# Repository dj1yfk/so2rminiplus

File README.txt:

SO2R MiniPlus - A simple and low cost SO2R controller

by Fabian Kurz, DJ5CW <fabian@fkurz.net>

Homepage:   https://fkurz.net/ham/so2rminiplus/
Repository: https://git.fkurz.net/dj1yfk/so2rminiplus

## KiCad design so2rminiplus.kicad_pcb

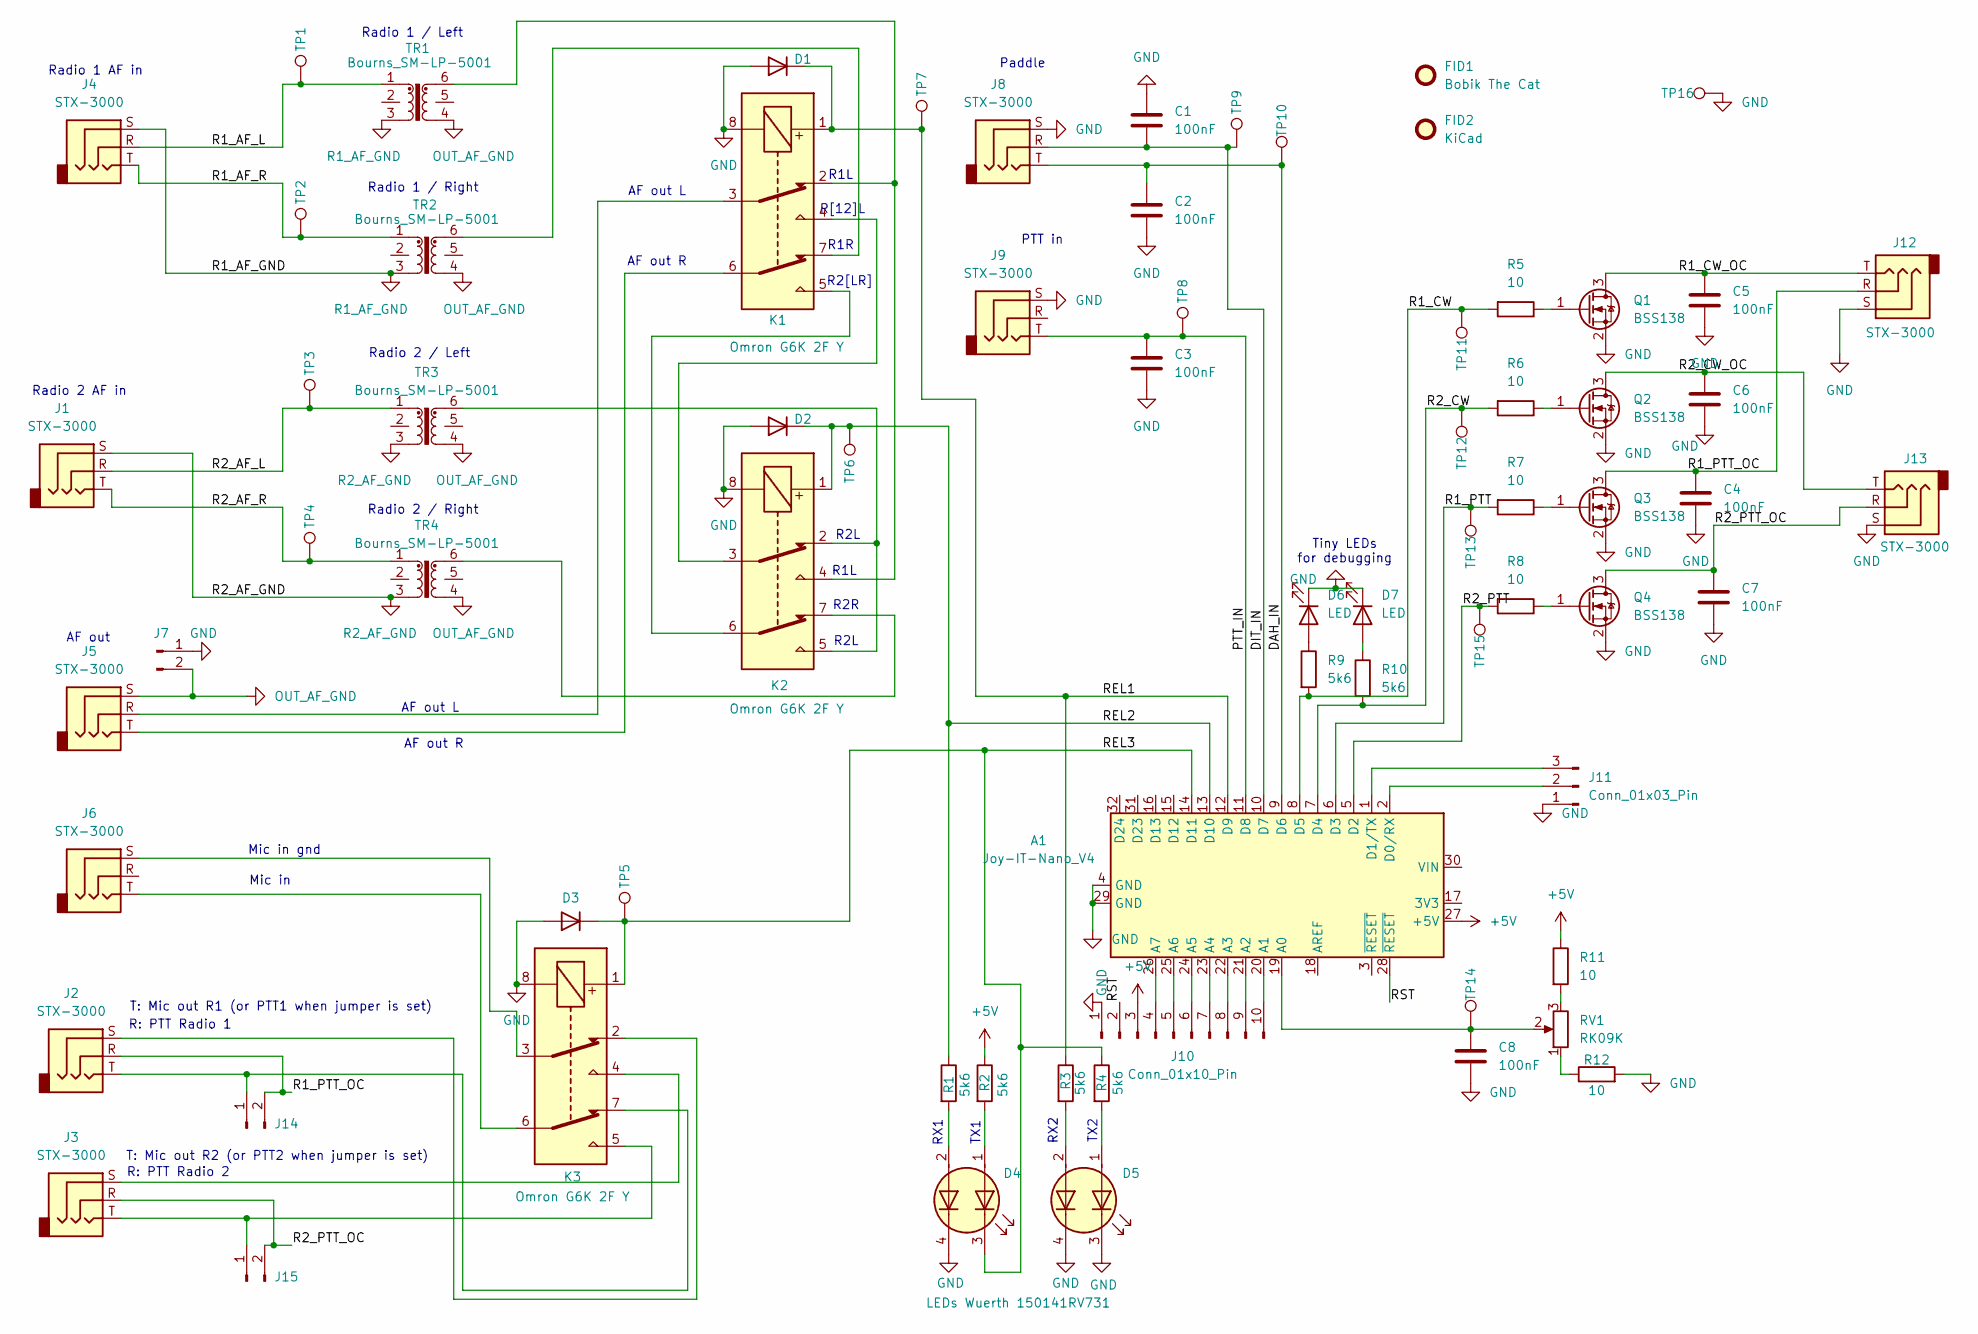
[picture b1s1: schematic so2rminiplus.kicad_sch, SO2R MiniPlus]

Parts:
A1: Joy-IT-Nano_V4; JoyIT-Nano-V4
C1, C2, C3, C4, C5, C6, C7, C8: 100nF; C_0603_1608Metric_Pad1.08x0.95mm_HandSolder
D1, D2, D3: D; D_SOD-123
D4: LEDs Wuerth 150141RV731; LED_RGB_Wuerth-PLCC4_3.2x2.8mm_150141M173100
D5: LED_Dual_AAKK; LED_RGB_Wuerth-PLCC4_3.2x2.8mm_150141M173100
D6, D7: LED; LED_0402_1005Metric_Pad0.77x0.64mm_HandSolder
FID1: Bobik The Cat; bobik
FID2: KiCad; KiCad-Logo2_5mm_SilkScreen
J1, J2, J3, J4, J5, J6, J8, J9, J12, J13: STX-3000; Jack_3.5mm_Kycon_STX-3000_Horizontal
J7, J14, J15: Conn_01x02_Pin; PinHeader_1x02_P2.54mm_Vertical
J10: Conn_01x10_Pin; PinHeader_1x10_P2.54mm_Vertical
J11: Conn_01x03_Pin; PinHeader_1x03_P2.54mm_Vertical
K1, K2, K3: Omron G6K 2F Y; Relay_DPDT_Omron_G6K-2F-Y
Q1, Q2, Q3, Q4: BSS138; SOT-23
R1, R2, R3, R4: 5k6; R_0603_1608Metric_Pad0.98x0.95mm_HandSolder
R5, R6, R7, R8, R11, R12: 10; R_0603_1608Metric_Pad0.98x0.95mm_HandSolder
R9, R10: 5k6; R_0402_1005Metric_Pad0.72x0.64mm_HandSolder
RV1: RK09K; Potentiometer_Alps_RK09K_Single_Horizontal
TP1, TP2, TP3, TP4, TP5, TP6, TP7, TP8, TP9, TP10, TP11, TP12, TP13, TP14, TP15, TP16: TestPoint; TestPoint_THTPad_1.0x1.0mm_Drill0.5mm
TR1, TR2, TR3, TR4: Bourns_SM-LP-5001; Transformer_Bourns_SM-LP-5001

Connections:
+5V: A1.27 (+5V), J10.3, R2.1, R11.1
/DAH_IN: A1.9 (D6), C2.1, J8.T, TP10.1
/DIT_IN: A1.10 (D7), C1.2, J8.R, TP9.1
/PTT_IN: A1.11 (D8), C3.1, J9.T, TP8.1
/R1_AF_L: J4.R, TP1.1, TR1.1
/R1_AF_R: J4.T, TP2.1, TR2.1
/R1_CW: A1.8 (D5), R5.2, R9.2, TP11.1
/R1_CW_OC: C5.1, J12.T, Q1.3 (D)
/R1_PTT: A1.6 (D3), R7.2, TP13.1
/R1_PTT_OC: C4.1, J2.R, J12.R, J14.2, Q3.3 (D)
/R2_AF_L: J1.R, TP3.1, TR3.1
/R2_AF_R: J1.T, TP4.1, TR4.1
/R2_CW: A1.7 (D4), R6.2, R10.2, TP12.1
/R2_CW_OC: C6.1, J13.T, Q2.3 (D)
/R2_PTT: A1.5 (D2), R8.2, TP15.1
/R2_PTT_OC: C7.1, J3.R, J13.R, J15.2, Q4.3 (D)
/REL1: A1.12 (D9), D1.1 (K), K1.1, R3.1, TP7.1
/REL2: A1.13 (D10), D2.1 (K), K2.1, R1.1, TP6.1
/REL3: A1.14 (D11), D3.1 (K), D4.3 (K1), K3.1, R4.1, TP5.1
/RST: A1.28 (~RESET), J10.2
GND: A1.4 (GND), A1.29 (GND), C1.1, C2.2, C3.2, C4.2, C5.2, C6.2, C7.2, C8.2, D1.2 (A), D2.2 (A), D3.2 (A), D4.4 (K2), D5.3 (K1), D5.4 (K2), D6.1 (K), D7.1 (K), J7.1, J8.S, J9.S, J10.1, J11.1, J12.S, J13.S, K1.8, K2.8, K3.8, Q1.2 (S), Q2.2 (S), Q3.2 (S), Q4.2 (S), R12.2, TP16.1
unnamed: A1.19 (A0), C8.1, RV1.2, TP14.1
unnamed: A1.20 (A1), J10.10
unnamed: A1.21 (A2), J10.9
unnamed: A1.22 (A3), J10.8
unnamed: A1.23 (A4), J10.7
unnamed: A1.24 (A5), J10.6
unnamed: A1.25 (A6), J10.5
unnamed: A1.26 (A7), J10.4
unnamed: A1.2 (D0/RX), J11.2
unnamed: A1.1 (D1/TX), J11.3
unnamed: D4.1 (A1), R2.2
unnamed: D4.2 (A2), R1.2
unnamed: D5.1 (A1), R4.2
unnamed: D5.2 (A2), R3.2
unnamed: D6.2 (A), R9.1
unnamed: D7.2 (A), R10.1
unnamed: J2.S, K3.2
unnamed: J3.S, K3.4
unnamed: J5.R, K1.3
unnamed: J5.T, K1.6
unnamed: J6.S, K3.3
unnamed: J6.T, K3.6
unnamed: J2.T, J14.1, K3.7
unnamed: J3.T, J15.1, K3.5
unnamed: K1.2, K2.4, TR1.6
unnamed: K1.4, K2.3
unnamed: K1.5, K2.6
unnamed: K1.7, TR2.6
unnamed: K2.2, K2.5, TR3.6
unnamed: K2.7, TR4.6
unnamed: Q1.1 (G), R5.1
unnamed: Q2.1 (G), R6.1
unnamed: Q3.1 (G), R7.1
unnamed: Q4.1 (G), R8.1
unnamed: R11.2, RV1.3
unnamed: R12.1, RV1.1
OUT_AF_GND: J5.S, J7.2, TR1.4, TR2.4, TR3.4, TR4.4
R1_AF_GND: J4.S, TR1.3, TR2.3
R2_AF_GND: J1.S, TR3.3, TR4.3

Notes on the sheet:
Radio 1 AF in
T: Mic out R1 (or PTT1 when jumper is set)
RX1
R: PTT Radio 2
R2[LR]
Mic in gnd
Radio 1 / Left
TX1
PTT in
R1L
Radio 1 / Right
AF out L
Mic in
Radio 2 AF in
Tiny LEDs for debugging
R1R
RX2
Radio 2 / Right
T: Mic out R2 (or PTT2 when jumper is set)
R2L
Paddle
Radio 2 / Left
R[12]L
R: PTT Radio 1
AF out R
R2R
AF out
TX2

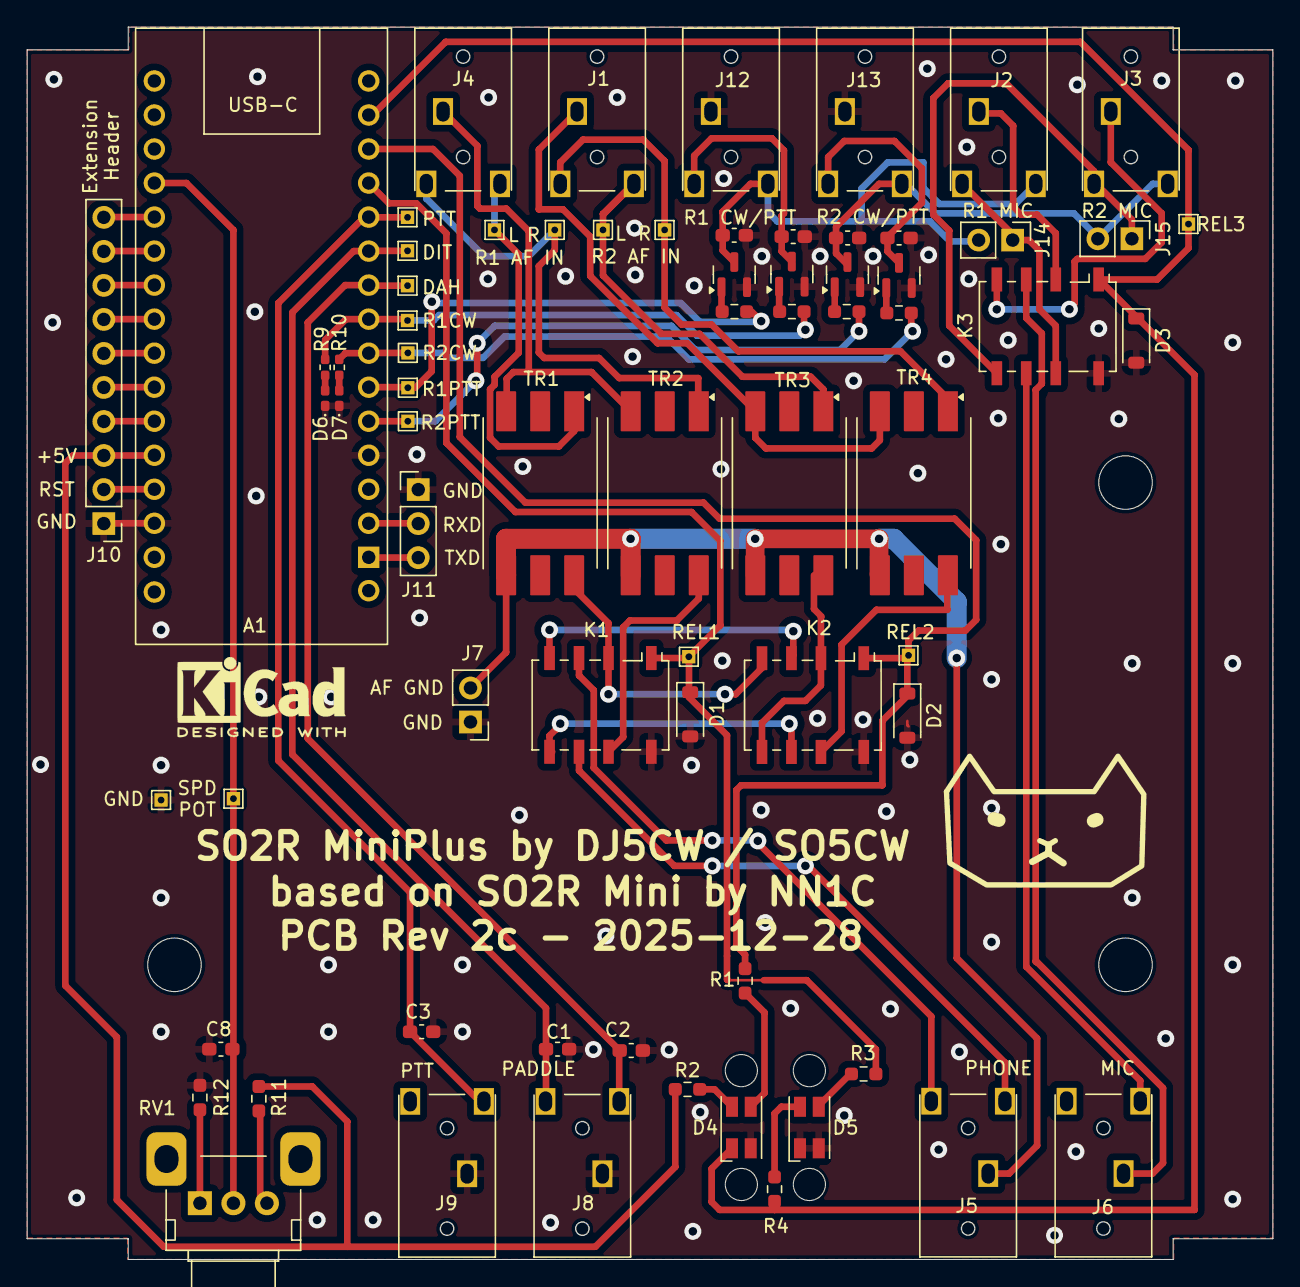
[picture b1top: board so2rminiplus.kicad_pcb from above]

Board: 2 copper layers, 93.0 x 91.9 mm, 73 parts (0 on the bottom side), 60 nets.

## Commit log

2025-08-24 Initial commit so2r mini plus rev2
2025-09-03 Make assembly layer more readable.
2025-12-18 Fix: Use correct part number for WUE dual colour LED
2025-12-18 Add README.txt with reference to project website and repository URL
2025-12-28 Fix swapped pins 4 and 7 on relay K3.
    Thanks to Peter, LA7WRA / LZ1VPC for finding this!
2026-05-23 Add front and rear panels
